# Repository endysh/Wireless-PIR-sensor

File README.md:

Wireless-PIR-sensor
===================

The project was stared with a goal of creating a low-cost wireless PIR sensor by using Arduino compatible hardware and enclosure from already available cheap, less than $5, PIR lights you can find on eBay, like the following 
http://www.ebay.com/sch/i.html?_from=R40&_sacat=0&_nkw=wireless+pir+light+battery&_sop=15

### Features
- custom Arduino compatible hardware
- nrf24L01 2.4 GHz wireless module for communication
- 2+ years run time with 2 AA batteries

### Images

Top<br>

Back with PCB visible<br>

Unpopulated 2-layer PCB, front and back<br>

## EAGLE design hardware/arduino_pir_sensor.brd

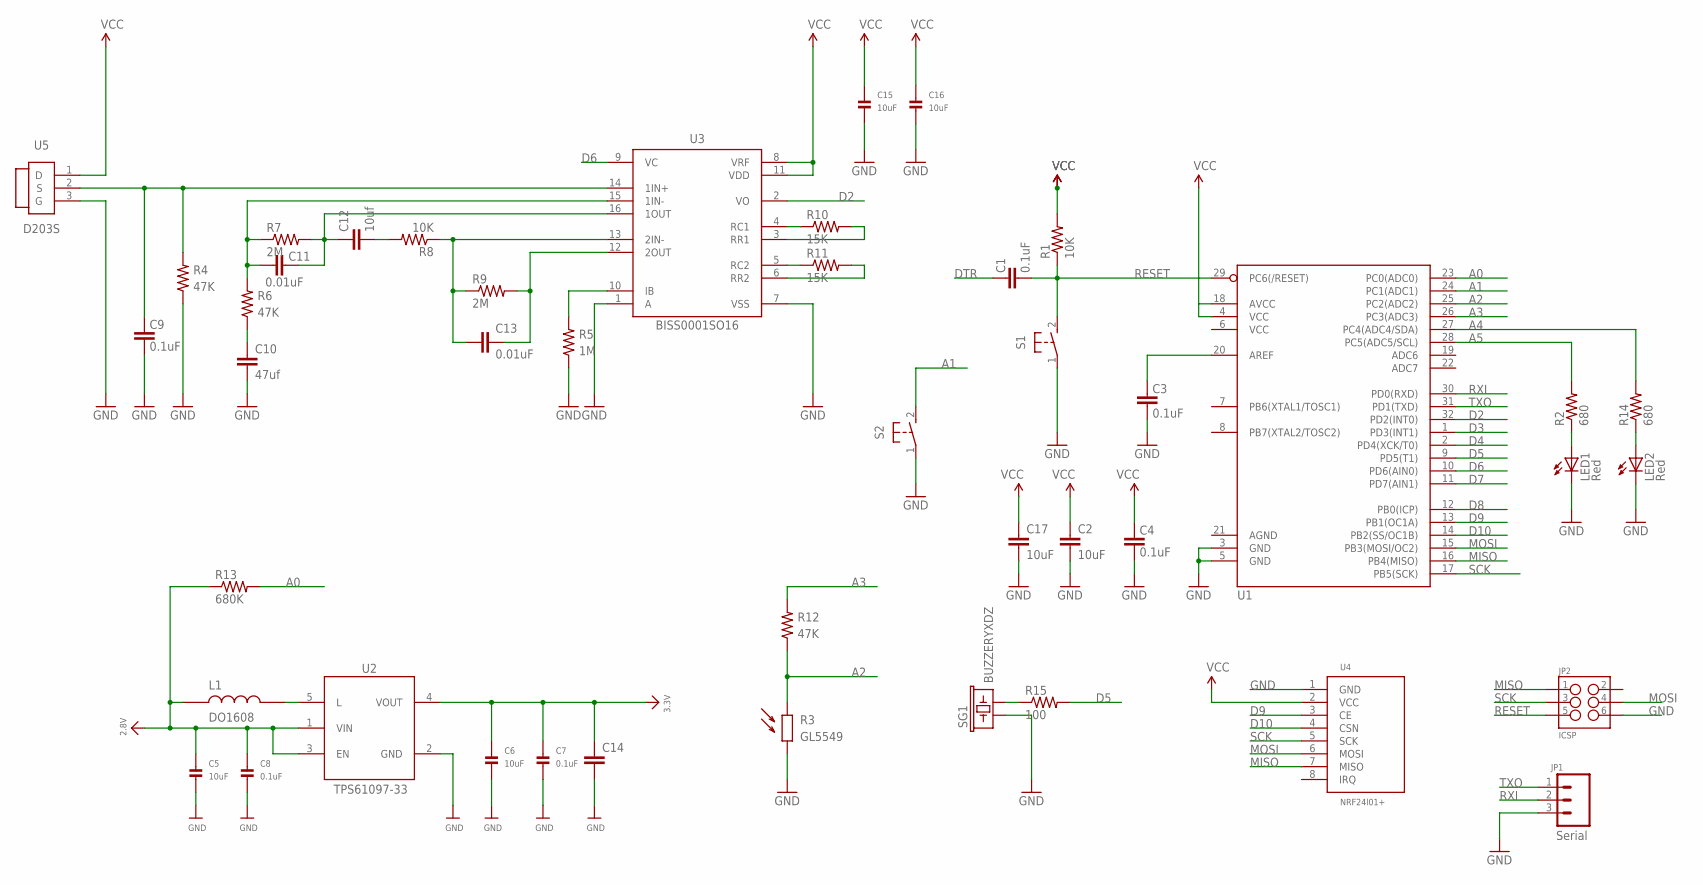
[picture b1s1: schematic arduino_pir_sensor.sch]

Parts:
C1, C3, C4, C9: 0.1uF; 0603-CAP; MPN 02016D104KAT2A
C2, C5, C6, C15, C16, C17: 10uF; 1206
C7, C8: 0.1uF; 0603
C10: 47uf; 0805
C11, C13: 0.01uF; 0603-CAP
C12: 10uf; 0805
C14: CAPPTH; CAP-PTH-SMALL
JP1: Serial; 1X03
JP2: ICSP; 2X3_POGO
L1: DO1608
LED1: Red; LED-0603
LED2: Red; LED5MM
R1, R8: 10K; 0603-RES
R2, R14: 680; 0603-RES
R3: GL5549; PHOTCELL
R4, R6, R12: 47K; 0603-RES
R5: 1M; 0603-RES
R7, R9: 2M; 0603-RES
R10, R11: 15K; 0603-RES
R13: 680K; 0603-RES
R15: 100; 0603-RES
S1, S2: TAC_SWITCH_SPST-6X3; TACTILE_SMD_6X3
SG1: BUZZERYXDZ; BUZZER-12MM-7.65
U1: ATMEGA328_SMT; TQFP32-08
U2: TPS61097-33; SOT-23-5L
U3: BISS0001SO16; SO-16
U4: NRF24L01+_MODULE; NRF24L01+MODULE
U5: D203S; TO5

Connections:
2.8V: C5.1, C8.1, L1.P$1 (1), R13.1, U2.1 (VIN), U2.3 (EN)
3.3V: C2.1, C4.2, C6.1, C7.1, C14.1, C15.1, C16.1, C17.1, R1.2, U1.4 (VCC), U1.18 (AVCC), U2.4 (VOUT), U3.8 (VRF), U3.11 (VDD), U4.2 (VCC), U5.1 (D)
A0: R13.2, U1.23 (PC0(ADC0))
A1: S2.2, U1.24 (PC1(ADC1))
A2: R3.P$1, R12.1, U1.25 (PC2(ADC2))
A3: R12.2, U1.26 (PC3(ADC3))
A4: R14.2, U1.27 (PC4(ADC4/SDA))
A5: R2.2, U1.28 (PC5(ADC5/SCL))
D2: U1.32 (PD2(INT0)), U3.2 (VO)
D3: U1.1 (PD3(INT1))
D4: U1.2 (PD4(XCK/T0))
D5: R15.2, U1.9 (PD5(T1))
D6: U1.10 (PD6(AIN0)), U3.9 (VC)
D7: U1.11 (PD7(AIN1))
D8: U1.12 (PB0(ICP))
D9: U1.13 (PB1(OC1A)), U4.3 (CE)
D10: U1.14 (PB2(SS/OC1B)), U4.4 (CSN)
DTR: C1.2
GND: C2.2, C3.1, C4.1, C5.2, C6.2, C7.2, C8.2, C9.1, C10.2, C14.2, C15.2, C16.2, C17.2, JP1.3, JP2.P$6 (6), LED1.C, LED2.K (C), R3.P$2, R4.1, R5.1, S1.1, S2.1, SG1.- (2), U1.3 (GND), U1.5 (GND), U2.2 (GND), U3.1 (A), U3.7 (VSS), U4.1 (GND), U5.3 (G)
MISO: JP2.P$1 (1), U1.16 (PB4(MISO)), U4.7 (MISO)
MOSI: JP2.P$4 (4), U1.15 (PB3(MOSI/OC2)), U4.6 (MOSI)
unnamed: L1.P$2 (2), U2.5 (L)
unnamed: C9.2, R4.2, U3.14 (1IN+), U5.2 (S)
unnamed: LED1.A, R2.1
unnamed: C3.2, U1.20 (AREF)
unnamed: R5.2, U3.10 (IB)
unnamed: C10.1, R6.1
unnamed: C11.2, R6.2, R7.1, U3.15 (1IN-)
unnamed: C11.1, C12.1, R7.2, U3.16 (1OUT)
unnamed: C12.2, R8.2
unnamed: C13.1, R8.1, R9.1, U3.13 (2IN-)
unnamed: C13.2, R9.2, U3.12 (2OUT)
unnamed: R11.1, U3.5 (RC2)
unnamed: R10.1, U3.4 (RC1)
unnamed: R10.2, U3.3 (RR1)
unnamed: R11.2, U3.6 (RR2)
unnamed: R15.1, SG1.+ (1)
unnamed: LED2.A, R14.1
RESET: C1.1, JP2.P$5 (5), R1.1, S1.2, U1.29 (PC6(/RESET))
RXI: JP1.2, U1.30 (PD0(RXD))
SCK: JP2.P$3 (3), U1.17 (PB5(SCK)), U4.5 (SCK)
TXO: JP1.1, U1.31 (PD1(TXD))

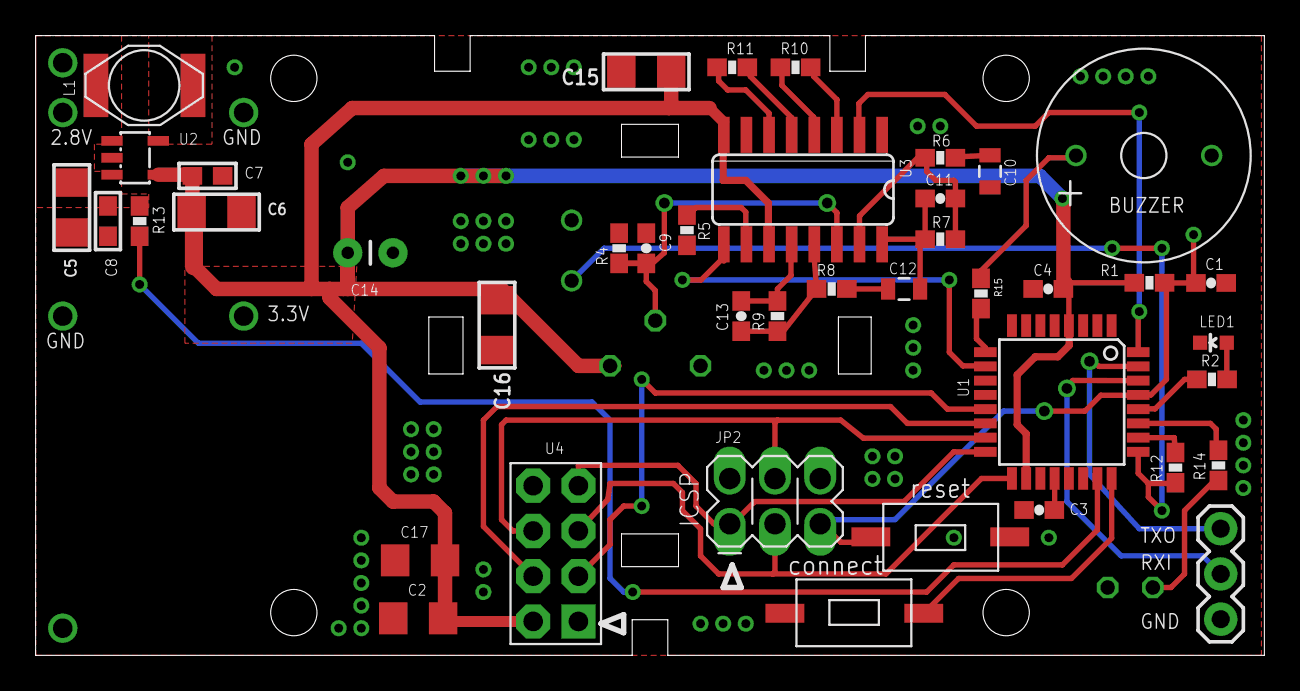
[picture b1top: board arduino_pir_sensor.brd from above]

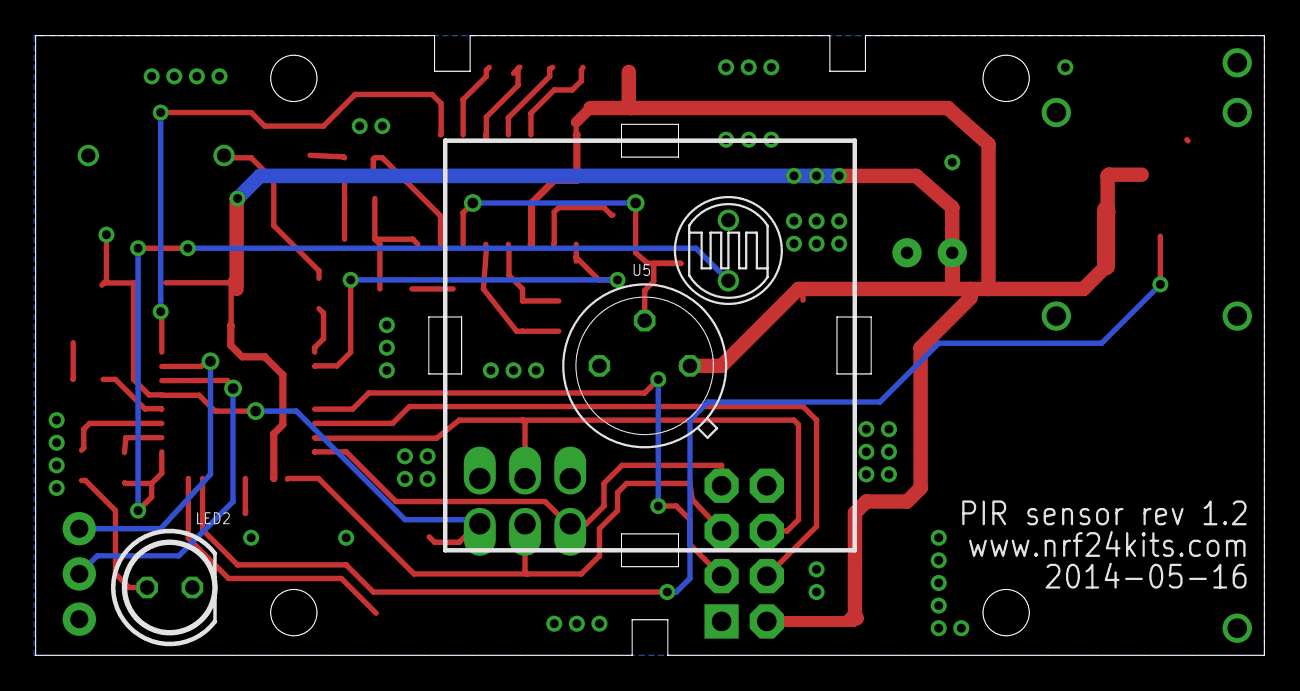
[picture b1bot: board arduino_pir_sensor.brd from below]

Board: 2 copper layers, 69.0 x 34.8 mm, 45 parts (3 on the bottom side), 37 nets.

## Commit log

2014-05-16 - initial check in - revision 1.0
    This program sends a single byte command with ASCII value 'o' to the preconfigured node
    when motion is detected and reported by PIR mode, then waits for 5 sec before it reads PIR sensor output again.
    No power saving techniques is used in this version, thus the current power consumption makes it not very suitable for
    operation from a battery
2014-05-16 images
2014-05-16 Update README.md
    - images added
2014-05-16 - pdf image for schematics added - frame to schematics added
2014-05-16 - minor code cleanup
2014-05-16 - cutout in ground planes on all PCB layers added below wireless module antenna - serial communication connector added
2014-05-16 - labels font type changed to vector
2014-05-16 - schematic pdf file updated
2014-05-18 - switching to power saving techniques
    // This program puts MCU in sleep mode and uses two interrupts to process events in order to save energy
    // The first interrupt is generated by PIR sensor output connected to D2 input, the interrupt handler schedules
    // transmission of a single byte command with ASCII value of 'o' and disables PIR sensor for a number of WDT interrupts
    // The second interrupt is generated by WDT and it fires about every 8 sec.
    // This interrupt handler decreases PIR sensor disable counter
2014-05-18 - extra power line capacitor added - "connect" button moved away from the mounting screw
2014-06-10 change value of the photo cell divider resistor to 47K from 510K
2014-06-11 Example wireless PIR sensor for MySensors IoT network initial checkin, does not send battery and light levels yet
2014-06-13 - send battery level and light level reports every 60 minutes
2014-06-18 - suppress "motion detected" events for ~4 min after a report has been send
2014-06-18 - resistor values fixed
2014-09-15 - minor reroute power lines for BISS0001 - contact pads for external power supply added
2014-11-06 - minor code cleanup - more comments

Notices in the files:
parts and their libraries:
SparkFun-DigitalIC: Licensing: CC v3.0 Share-Alike You are welcome to use this library for commercial purposes.
microbuilder: This work is placed in the public domain, and may be freely used for commercial and non-commercial work with the following conditions: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
